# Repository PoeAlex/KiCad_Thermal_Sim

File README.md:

# KiCad Thermal Sim - Fast Multi-Layer Copper Thermal Simulation for KiCad

**KiCad Thermal Sim** is a lightweight KiCad PCB Editor plugin for fast, layout-oriented **heat spreading simulation across all copper layers** (`F.Cu` to `B.Cu`, including inner layers).

This is **not** a full 3D CFD/FEA solver. It is intended as a practical engineering tool to quickly answer:

- Where are the **hotspots** on each copper layer?
- How much do **copper pours/planes** and **via stitching** help?
- Which layout variant is **better** in an A/B comparison?
- How does heat distribute through the **stackup**?
- How much extra heat is created by **DC current flow** in copper?
- Which grid settings were actually used when automatic coarsening protects runtime?

---

## What It Simulates

- **2D in-plane conduction** on each copper layer.
- **Vertical coupling** between adjacent copper layers through FR4 and via enhancement.
- **Manual power injection** from explicitly configured **Heat Sources**.
- Constant pad power and time-varying **PWL power profiles**.
- Optional **DC current-flow heating** from source/sink pads on KiCad nets.
- **Convection** to ambient on top and bottom outer surfaces.
- Optional **Thermal Pad** geometry on `User.Eco1` for stronger bottom-side heat removal.
- Current-path diagnostics: copper loss, effective resistance, equivalent voltage drop, grid quality, and a Joule loss map.

---

## Installation

### Option A: KiCad Plugin Manager

1. Download the latest `ThermalSim-vX.Y.Z.zip` from the [Releases](https://github.com/PoeAlex/KiCad_Thermal_Sim/releases) page.
2. In KiCad, open **Plugin and Content Manager**.
3. Click **Install from File...** and select the downloaded ZIP.
4. Restart KiCad.
5. On first run, the plugin detects missing dependencies and offers to install them automatically.

### Option B: Manual Copy

1. Download or clone this repository.
2. Copy the plugin folder, meaning the folder that contains `__init__.py`, `thermal_plugin.py`, and the other `.py` modules, into KiCad's plugin directory:

   - **Windows**: `%APPDATA%\kicad\9.0\scripting\plugins\`
   - **Linux**: `~/.local/share/kicad/9.0/scripting/plugins/`
   - **macOS**: `~/Library/Application Support/kicad/9.0/scripting/plugins/`

3. Restart KiCad.
4. On first run, the plugin offers to install missing packages (`numpy`, `scipy`, `matplotlib`) automatically.

Alternatively, install packages manually in the **KiCad 9.0 Command Prompt**:

```bash
pip install numpy scipy matplotlib
```

Optional for faster large solves on supported Windows/Linux x86_64 systems:

```bash
pip install pypardiso
```

Run the plugin in PCB Editor via **Tools -> External Plugins -> 2.5D Thermal Sim**.

---

## Quick Start

1. Open your PCB in **KiCad PCB Editor**.
2. Select one or more pads if you want to pre-fill manual heat sources.
3. Run **Tools -> External Plugins -> 2.5D Thermal Sim**.
4. In **Heat Sources**, create one named source from the KiCad selection or the searchable board-pad browser. Enter its total loss in watts (or a total-power PWL file) and choose how it is split across its pads.
5. Set **Duration**, **Ambient**, and **Resolution** on the **Overview** tab.
6. Optionally use **Current Heating** to create a net path, select where current enters and leaves that net, and enter the positive path current. Use **New DC Circuit** for linked forward and return paths with one shared current value.
7. Optionally use **Advanced** for the simulation area, thermal pad, convection, and solver settings.
8. Click **Preview** to check the mapped geometry, then **Run**.

---

## GUI Settings

The resizable dialog keeps board context and live preflight status visible above and below four compact tabs:

- **Overview** - duration, ambient temperature, target cell size, compute budget, live cost estimate, output, and collapsible board details.
- **Heat Sources** - manual heat sources selected independently from current terminals.
- **Current Heating** - DC current source/sink terminals for Joule heating.
- **Advanced** - collapsible simulation-area, thermal-pad, and solver settings.

The header summarizes the board, copper-layer count, heat sources, and current-balance state. The fixed footer shows the requested versus actual grid, readiness warnings, and the main **Preview** and **Run Simulation** actions. Help and settings import/export are available from **More**. After a successful run, the dialog retains maximum temperature, elapsed time, and shortcuts to the report and output folder.

### Overview Tab

#### Board Info

Shows detected copper layers with thicknesses and dielectric gaps parsed from the board stackup. Pads selected when the dialog opened are shown only as a convenience; simulation roles are configured in **Heat Sources** and **Current Heating**.

#### Main Settings

- **Duration (sec)** - total simulated time. Shorter durations emphasize transient peaks; longer durations approach quasi steady-state.
- **Ambient Temp (C)** - reference temperature. Results are relative to ambient.
- **Target Cell Size (mm)** - desired spatial grid size. Smaller values improve hotspot and trace localization but increase runtime.
- **Compute Budget** - choose **Fast**, **Balanced**, **Detailed**, **Very detailed**, or **Custom**. The budget is based on total solver nodes across all copper layers.
- **Maximum Solver Nodes** - available in Custom mode for an explicit upper
  limit of up to 100 million equivalent uniform nodes. Values above 10 million
  are expert settings and may require tens of GB of RAM before adaptive
  reduction.

The live estimate shows requested versus actual cell size, grid dimensions, total nodes, approximate resolvable feature size, memory range, and a relative runtime class. For large boards, ThermalSim may automatically coarsen the requested cell size to remain within the selected budget. The report records the requested and actual resolution, compute budget, and simulated board fraction.

#### Output

- **Show All Layers** - display results for all copper layers.
- **Save Snapshots** - store intermediate temperature images.
- **Snapshot Count** - number of intermediate snapshots.
- **Output Folder** - where the timestamped result folder is created.

#### Settings Files

- **Load Settings...** - load a JSON settings file from any folder and apply it to the open dialog.
- **Save Settings...** - save the current dialog values as a JSON settings file.

ThermalSim separates machine preferences from board-specific electrical intent:

- `thermal_sim_last_settings.json` keeps last-used simulation, output, mesh, and solver preferences.
- `<board-name>.thermalsim.json`, next to the `.kicad_pcb` file, keeps schema-v3 heat sources, current paths, and DC circuits for that board. It is updated on Preview, Run, and when a changed dialog is closed.
- **Load Settings...** and **Save Settings...** remain available for explicit experiment files.

Pad references prefer KiCad UUIDs and retain footprint/pad fallbacks, so moving a pad or changing its net code does not normally break the project configuration. Missing schema-v3 references are shown as needing repair and block execution. Older schema-v2 settings are promoted automatically only when all referenced pads can be resolved; otherwise the legacy entries remain available in the advanced editor and are never silently rebound to a different pad.

### Heat Sources Tab

Manual component/package loss is configured separately from current-flow terminals. A heat source owns one total power profile and one or more pads:

1. Enter a source name and a total constant loss or PWL path.
2. Choose **By pad area**, **Equal**, or **Custom shares**.
3. Click **Add KiCad Selection**, or use **Browse Board** to search every board pad by reference, pad number, pin function, net, layer, or area.
4. Select a source row to edit its name, total profile, distribution, or custom shares.

For example, a `2 W` source assigned to two pads with normalized area shares `0.25 / 0.75` injects `0.5 W / 1.5 W`; the source total is never multiplied by the number of pads. A PWL file is likewise interpreted as the source's total time-varying power and scaled by the same shares.

**Advanced Pad Allocation** retains the earlier per-pad editor for imported or unusual configurations. Existing schema-v2 `power_pads` settings are converted into named sources when they can be resolved safely.

#### PWL File Format

PWL files are LTspice-style text files with two columns:

```text
; Comment lines start with ; or *
; Time(s)  Power(W)
0.0        0.0
0.001      1.0
0.005      2.5
0.010      2.5
0.020      0.0
```

- Time is in seconds.
- Power is in watts.
- Time values must be monotonically increasing.
- Power is linearly interpolated between points and held at the first/last value outside the defined range.

### Current Heating Tab

Enable current heating to calculate copper losses from DC current flow. The guided editor uses a positive path current; signed per-pad terminals are generated automatically:

1. Click **New Net Path** and enter the path current.
2. Select pads and click **Selection Enters**, then select the opposite endpoints and click **Selection Leaves**. **Browse Board** offers the same searchable pad list and locks to the first selected net.
3. Keep equal sharing or enter custom comma-separated shares for either endpoint side.
4. For a complete loop, click **New DC Circuit**. The linked forward and return paths share one current value but may use different KiCad nets.

Every individual path is restricted to one net. The same pad cannot be on both endpoint sides, and ThermalSim normalizes the shares so the generated terminals balance exactly. A `5 A` path with one entering pad and two equally shared leaving pads becomes `+5 A, -2.5 A, -2.5 A` internally. Incomplete paths remain visible with **Needs setup/repair** status and block Run rather than being guessed.

**Advanced Terminal Editor** retains direct signed per-pad entry for specialist and migrated configurations.

Current heating is additive with **Heat Sources**:

```text
total heat = manual pad power + calculated Joule copper loss
```

Power pads and current terminals may be different pads. Area limiting remains available with current heating: ThermalSim includes every pad, track, via/PTH, and filled zone belonging to the active current nets, then expands that geometry by the configured thermal margin. A large active plane may therefore require almost the full board.

The report shows **Path Current** as the useful current value. For a `+5 A` source and a `-5 A` sink, the path current is `5 A`. The internal sum of absolute terminal currents (`10 A` in that example) is kept only in raw diagnostics.

### Advanced Tab

#### Geometry Filters

- **Ignore Traces** - exclude copper traces from the conductivity map; zones, pours, and pads still contribute.
- **Limit to Active Sources and Current Paths** - crop the rectangular solver domain around heat sources and complete active current-net geometry.
- **Thermal Margin (mm)** - additional board area around sources and current paths. A practical starting point is 10-30 mm.

The preflight status shows the effective dimensions and percentage of the board. All copper inside the rectangular domain remains part of the thermal model. If active-net geometry cannot be inspected safely, ThermalSim falls back to the full board and reports a warning.

#### Thermal Pad (`User.Eco1`)

- **Enable Pad Simulation** - treat `User.Eco1` geometry as a thermal interface zone with enhanced bottom-side heat removal.
- **Pad Thickness (mm)** - thermal interface thickness.
- **Pad Cond. (W/mK)** - thermal interface conductivity.
- **Pad Heat Cap. (J/m2K)** - additional areal heat capacity.

#### Solver

- **Convection h (W/m2K)** - convection coefficient for top/bottom surfaces. Default is 10.
- **PCB Thickness (mm)** - overall board thickness. Stackup thickness is used when available.
- **Compute Engine** - `Auto` selects the matrix-free CPU engine for large jobs and keeps the legacy sparse solver for small jobs. Both engines remain manually selectable.
- **Spatial Mesh** - `Adaptive` keeps the requested cell size at copper edges, pads, vias, sources, and thermal-pad boundaries while merging homogeneous interiors. `Uniform` keeps the full regular grid.
- **Adaptive Max Cell Ratio** - largest adaptive cell relative to the requested cell size. The default is 8.
- **Capabilities** - detected solver backend, including the optional `thermalsim_core.dll`.

The **Balanced** compute budget is the default. Presets use total solver nodes, so a four-layer board automatically receives fewer 2D cells than a two-layer board at the same budget. **Custom** exposes one explicit maximum-node value; ThermalSim retains headroom when it must auto-coarsen.

The fast engine applies the finite-volume operator without constructing the
large global COO/CSR matrix used by the legacy direct solver. Adaptive runs use
a conservative reduced graph and geometrically coarsened multigrid
preconditioning. Reports show the equivalent uniform nodes, actual adaptive
nodes, reduction factor, PCG iterations, and residual.

---

## Preview

The **Preview** button generates a geometry visualization showing copper distribution, via regions, and the effective simulation-area boundary on each layer. Pad roles use a consistent legend: heat sources are yellow, current entering copper is red with an upward triangle, and current leaving copper is blue with a downward triangle. Its header reports the cropped dimensions and percentage of the board.

ThermalSim uses the copper-zone fills already stored by KiCad. If zones are
stale or unfilled, press **B** in PCB Editor before Preview or Run. The plugin
does not refill zones automatically because this can block the interface for
minutes on large boards and is unstable in some KiCad builds.

---

## Report Output

Each run creates a timestamped result folder, for example `Thermalsim_20260426_111121/`.

Typical files:

- `thermal_report.html` - main report with settings, stackup, diagnostics, images, and interactive heatmap.
- `thermal_preview.png` - mapped geometry preview.
- `thermal_stackup.png` or `thermal_final.png` - final temperature heatmap.
- `joule_loss_map.png` - current-induced copper loss map when current heating is active.
- `snap_*.png` - optional time-series snapshots.

### Current Path Diagnostics

When current heating is enabled, the HTML report includes **Current Path Diagnostics**:

- **Copper Loss** - total calculated Joule heating for active nets.
- **R_eff** - effective resistance, computed from `P / I_source^2`.
- **V_eq** - equivalent voltage drop, computed from `P / I_source`.
- **Source/Sink Current** - source and sink totals per active net.
- **Path Current** - useful current value for the path, not the doubled absolute terminal sum.
- **Net Path Metrics** - terminals, balance, loss, resistance, voltage drop, cell count, edge count, via edges, and copper islands.
- **Current Terminals** - pad positions, matched grid cells, island IDs, and mean potentials.
- **Mapped KiCad Primitives** - pads, tracks, vias/PTHs, zones, track length, and width summary.
- **Joule Loss Map** - per-layer static image of current-induced copper loss.

The report records requested and actual grid resolution, grid size, compute-budget preset, node budget, and the simulated percentage of the board.

---

## How to Interpret Results

This tool is most reliable for:

- **Relative comparisons** between layout variants.
- **Hotspot locations**.
- Trends from more copper, more vias, wider traces, or better spreading.
- Order-of-magnitude current-path loss and resistance diagnostics.

Absolute temperatures are **estimates** and depend strongly on modeling assumptions, grid resolution, board environment, airflow, and component/package thermal paths.

---

## Architecture

The plugin is split into focused modules:

| Module | Purpose |
|--------|---------|
| `capabilities.py` | Runtime detection of numpy, scipy, matplotlib, pypardiso, numba |
| `dependency_installer.py` | Auto-install dialog for missing packages via pip |
| `stackup_parser.py` | Parse copper/dielectric layers from `.kicad_pcb` S-expressions |
| `gui_dialogs.py` | wxPython dialog for simulation parameters |
| `geometry_mapper.py` | Accurately rasterize tracks, arcs, pads, vias, and filled zones |
| `adaptive_mesh.py` | Build conservative adaptive meshes and multigrid operators |
| `electrical_solver.py` | Solve DC current flow and convert copper losses to heat sources |
| `source_configuration.py` | Persist schema-v3 projects, resolve stable pad references, migrate legacy settings, and expand sources/paths |
| `thermal_solver.py` | Legacy sparse and matrix-free PCG/BDF2 thermal solvers |
| `native_core.py` | Load the optional Windows x64 C++/OpenMP CPU core |
| `pwl_parser.py` | Parse LTspice-style PWL power profiles |
| `visualization.py` | Generate thermal plots, previews, heatmap payloads, and Joule loss maps |
| `thermal_report.py` | Generate the HTML report |
| `thermal_plugin.py` | Orchestrate workflow and KiCad ActionPlugin integration |

---

## Limitations

- No explicit component/package thermal model; junction-to-case-to-pad behavior is not modeled.
- Convection is simplified as uniform top/bottom ambient coupling.
- Radiation is not modeled.
- Current-flow heating is static DC only; AC effects, skin effect, and temperature-dependent copper resistance are not modeled.
- Current-path accuracy depends on grid resolution; narrow traces and small pads may need a finer grid to match hand calculations closely.
- Very fine requested resolutions may be auto-coarsened when the selected compute budget is exceeded.
- Via coupling is an approximation.
- Results depend strongly on **Target Cell Size**, **Compute Budget**, and the selected simulation area and thermal margin.
- Thermal Pad (`User.Eco1`) is a simplification of real contact pressure, interface quality, and sink temperature.

---

## Suggested Workflow

1. Add manual dissipating components in **Heat Sources**.
2. Add source/sink terminals in **Current Heating** only when copper `I^2R` heating matters.
3. Press **B** in PCB Editor so every copper zone has a current fill.
4. Enable **Limit to Active Sources and Current Paths** and start with a moderate thermal margin, for example 20 mm.
5. Check the effective board percentage; active current nets are always included completely.
6. Tune **Target Cell Size** until hotspots and current-path metrics are stable. Try 0.5 mm, then 0.3 mm.
7. Increase the **Compute Budget** only after checking the live node, memory, and runtime estimate.
8. Commit the board's `.thermalsim.json` sidecar with the KiCad project for repeatable comparisons; use **Save Settings...** for experiment-specific copies.
9. Compare layout variants using the same settings.
10. Validate important designs with measurement or a full 3D thermal workflow.

---

## Testing

Run the test suite from the repository root:

```bat
run_tests.bat
```

Run the synthetic large-grid benchmark without a proprietary board file:

```bash
python benchmark_fast_engine.py --nodes 10000000 --layers 4 --solve-steps 3
```

Legacy matrix construction is automatically skipped above the configured
safety limit. The benchmark reports equivalent/adaptive node counts, operator
build times, solve time, iteration counts, and process memory.

To build the optional native Windows CPU core, install Visual Studio Build
Tools with the C++ workload, then run:

```bash
cmake -S native -B native/build
cmake --build native/build --config Release
```

The generated `native/bin/thermalsim_core.dll` is included automatically by
`build_pcm_package.py`. Without the DLL, the same fast-engine interface uses
the NumPy/SciPy CPU implementation.

Useful variants:

```bat
run_tests.bat -k "test_thermal_solver"
run_tests.bat -m physics
run_tests.bat --cov=ThermalSim
```

### Real KiCad Benchmark

Use KiCad's bundled Python to benchmark a real board without saving or modifying it:

```powershell
& "C:\Program Files\KiCad\9.0\bin\python.exe" benchmark_real_board.py `
  "C:\path\to\board.kicad_pcb" --scenario thermal --time-stepping auto
```

Set `THERMALSIM_HEADLESS=1` when importing ThermalSim as a library outside PCB Editor. This prevents ActionPlugin registration while keeping the solver and board readers available.

---

## License / Disclaimer

MIT License

This plugin provides engineering estimates intended for fast iteration and comparative analysis. For safety-critical or thermally constrained designs, validate with measurement and/or a full 3D thermal tool.

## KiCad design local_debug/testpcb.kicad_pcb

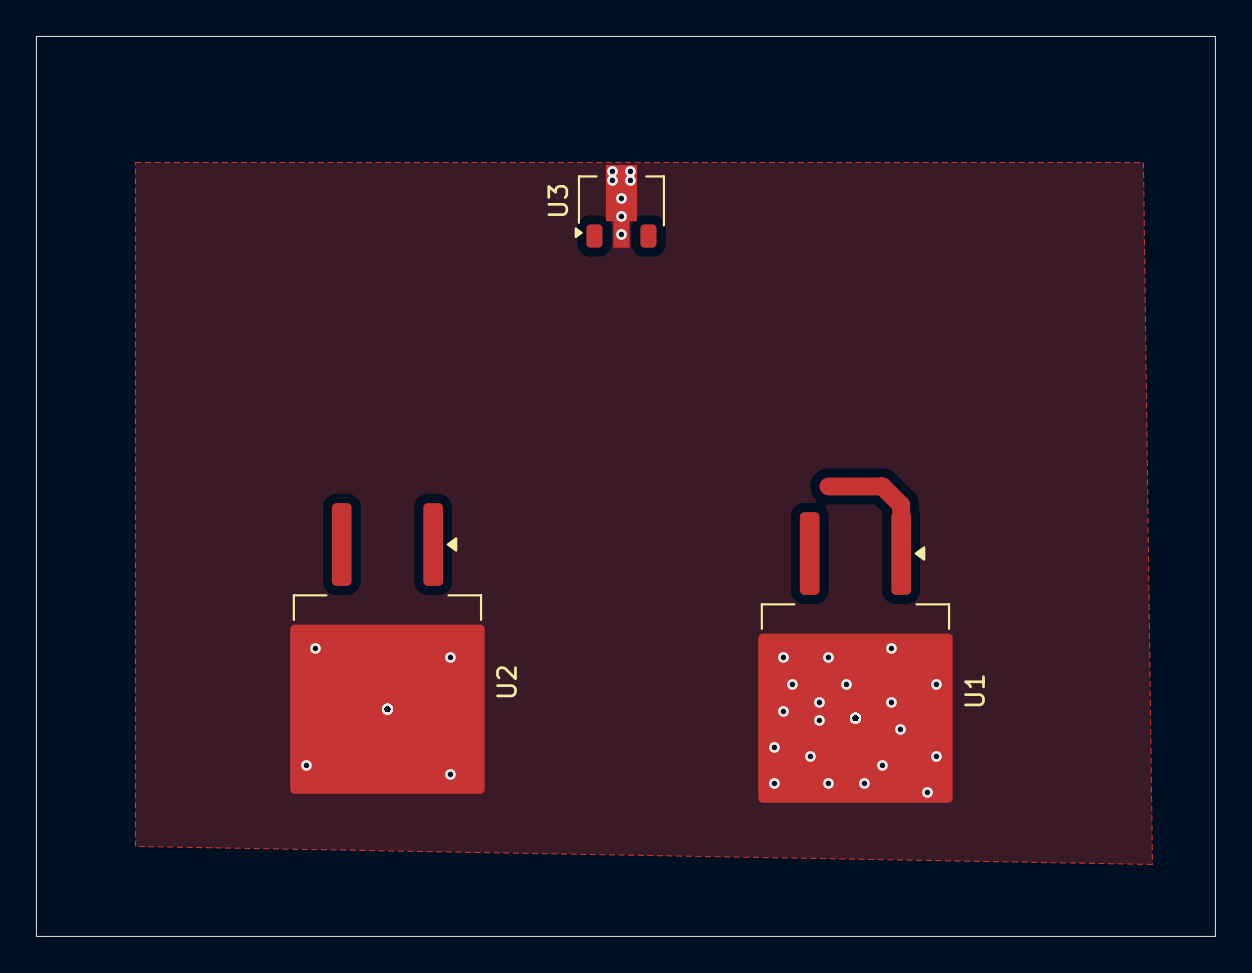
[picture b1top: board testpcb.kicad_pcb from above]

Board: 6 copper layers, 65.5 x 50.0 mm, 3 parts (0 on the bottom side), 4 nets.

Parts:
U1, U2: LM337_TO263; TO-263-2
U3: L79L08_SOT89; SOT-89-3

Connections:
GND: U1.2 (VI), U2.2 (VI), U3.2 (VI)
unnamed: U1.1 (ADJ), U3.3 (VO)
unnamed: U1.3 (VO), U2.1 (ADJ)
unnamed: U2.3 (VO), U3.1 (GND)

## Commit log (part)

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2026-01-03 First minimal code
2026-01-03 feat: add preview button to settings dialog and refactor layer detection and feature processing
    layer detection still missing inner layer
2026-01-03 Fix zone layer detection for inner copper
2026-01-03 Detect zones with IsOnLayer for inner copper
2026-01-03 Rasterize zone polygons for copper mapping
2026-01-03 Use filled polygons to rasterize zones
2026-01-03 Fallback to zone outlines for polygon fills
2026-01-03 Account for zone cutouts in rasterization
2026-01-03 polygon readout fixed
2026-01-04 Add geometry filters and stackup snapshots
2026-01-04 feat: Optimize thermal simulation with NumPy slicing, add Numba import check, remove 'ignore polygons' option, and refine time step and diffusion parameters.
2026-01-04 Fix copper layer stackup ordering
2026-01-04 Include missing inner copper layers
2026-01-04 Ensure full copper layer stack
2026-01-04 Repair copper layer detection
2026-01-04 feat: improve copper layer detection by explicitly identifying F.Cu and B.Cu and ordering layers from front to back.
2026-01-04 code cleanup
    Thermal simulation optimization
    Readme
2026-01-04 images added
2026-01-05 proper layer order read and cupper thickness extraction
2026-01-05 copper thickness readout fix
2026-01-06 Use stackup thicknesses in simulation
2026-01-06 Use stackup copper and dielectric thickness in simulation
2026-01-06 Add HTML report with settings and images
2026-01-06 Use per-layer stackup values in solver
2026-01-06 Refine solver scaling and heat capacity
2026-01-06 Stabilize diffusion scaling by max K
2026-01-06 Enhance preview overlays for pads and heatsink
2026-01-06 Tweak preview overlays and UI labels
2026-01-06 Add snapshot timing and report gallery
2026-01-06 Fix snapshots and add per-run output folders
2026-01-06 Fix snapshot diagnostics and output settings
2026-01-06 Fix snapshot listing in report
2026-01-06 gui picture update
2026-01-07 Apply no-flux boundary in thermal solver
2026-01-07 Switch thermal solver to implicit matrix-free method
2026-01-07 Tighten pad masking fallback handling
2026-01-07 Handle KiCad angle types in pad masking
2026-01-07 Tune timestep and layer thickness for diffusion
2026-01-07 Improve thermal model accuracy
2026-01-07 Fix thickness map array indexing
2026-01-07 Fix thickness map broadcasting
2026-01-07 Implement implicit sparse thermal solver
2026-01-07 Add scipy steady-state solver for realistic temps
2026-01-07 Add SciPy steady-state solver for thermal accuracy
2026-01-07 Use optional Pardiso solver for steady-state
2026-01-07 Require SciPy and report Pardiso usage
2026-01-07 Add scipy steady-state solver with optional pardiso
2026-01-07 Add SciPy steady-state solver reporting
2026-01-07 Switch to implicit sparse time stepping
2026-01-07 Optimize implicit solver progress and RHS
2026-01-07 Implement implicit BDF2 thermal solver
2026-01-07 Replace explicit solver with implicit BDF2 FVM
2026-01-07 Add energy balance diagnostics to solver
2026-01-07 Fix energy balance interval integration
2026-01-07 Optimize transient stepping with multirate phases
2026-01-07 Fix missing steps references in solver debug
2026-01-08 Gate multiphase solves and fix energy balance
2026-01-08 Fix output flow and pad capacitance
2026-01-08 Fix report details and progress handling
2026-01-08 Update installation instructions for Matplotlib
2026-01-08 Update title for thermal simulation clarity
2026-01-18 Add PCM package layout and metadata
    Note: ZIP package not generated because Codex Web cannot commit binaries.
2026-01-19 adpapted metadata.json
2026-01-19 Delay optional deps until plugin run
2026-02-07 current state
2026-02-07 updated screenshots
2026-02-07 Remove building and testing sections from README
    Removed sections on building the PCM package and testing from the README.
2026-02-08 added licencse file
2026-02-14 current path debugging
2026-03-16 Redesign thermal report layout
2026-03-19 Enhance thermal report interactivity and print layout
2026-03-19 Speed up simulation initialization and add coverage tests
2026-04-24 Add optional PyPardiso install checkbox
2026-04-24 Add installer progress status feedback
2026-04-24 Add English current paths UI with per-pad heating
2026-04-26 Add electrical solver diagnostics
2026-04-26 Separate power pads from current terminals
2026-04-26 Update README for power pads and current path diagnostics
2026-04-26 Update docs and screenshots for new tabs
2026-04-26 Add manual load and save for ThermalSim settings
2026-04-27 Document expert grid limits and settings persistence
